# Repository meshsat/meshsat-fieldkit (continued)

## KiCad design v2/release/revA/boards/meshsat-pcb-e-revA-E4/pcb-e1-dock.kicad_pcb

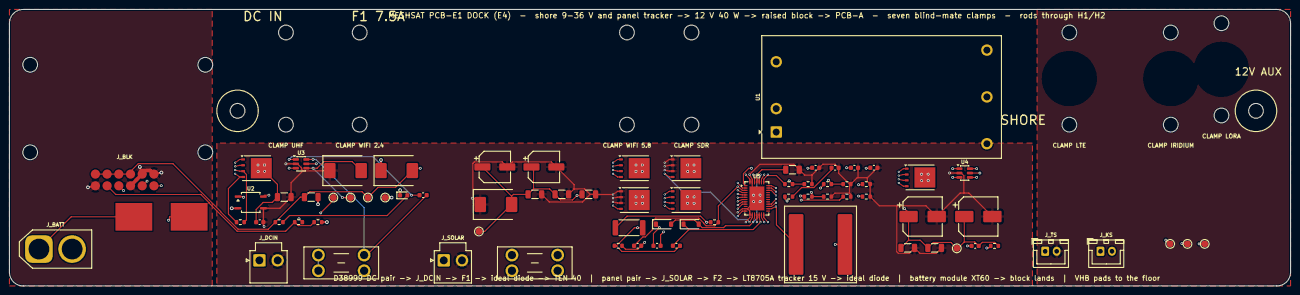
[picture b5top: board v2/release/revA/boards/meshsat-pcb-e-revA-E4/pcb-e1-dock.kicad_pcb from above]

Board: 4 copper layers, 278.0 x 60.0 mm, 97 parts (0 on the bottom side), 44 nets.

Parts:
C1, C13, C14: 10u 50V; C_1206_3216Metric
C2, C23: 100n; C_0603_1608Metric
C3: 22u 25V; C_1206_3216Metric
C4, C28: 100n 50V; C_0603_1608Metric
C11, C12: 100u 35V Panasonic EEHZK1V101XP hybrid polymer (7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; CP_Elec_6.3x7.7
C15: 4.7u 50V; C_1206_3216Metric
C16: 1n; C_0603_1608Metric
C17, C18: 470n 25V; C_0603_1608Metric
C19: 4.7u 25V; C_1206_3216Metric
C20: 1u; C_0603_1608Metric
C21: 4.7n; C_0603_1608Metric
C22: 100p; C_0603_1608Metric
C24, C25: 39u 35V Panasonic 35SVPF39M polymer (6.9 mm); CP_Elec_8x6.7
C26, C27: 10u 25V; C_1206_3216Metric
D1: SMCJ33A (input surge, datasheet 50 V 100 ms); D_SMC
D3: SMCJ15A; D_SMC
D4: SMCJ33A (panel surge); D_SMC
D5: BAT54 boost diode INTVCC -> BOOST1; D_SOD-123
D6: BAT54 boost diode INTVCC -> BOOST2; D_SOD-123
F1: 7.5 A mini blade (Keystone 3568 holder, in the cl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; Fuseholder_Blade_Mini_Keystone_3568
F2: 10 A mini blade (Keystone 3568 holder, in the cle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; Fuseholder_Blade_Mini_Keystone_3568
H1, H2: M3 rod pass-through, PCB-A standoff stands here; MountingHole_3.2mm_M3
H3, H4, H5, H6: M3 standoff, raised block; MountingHole_3.2mm_M3
H7, H8: M3, float clamp UHF; MountingHole_3.2mm_M3
H9, H10: M3, float clamp WIFI 2.4; MountingHole_3.2mm_M3
H11, H12: M3, float clamp WIFI 5.8; MountingHole_3.2mm_M3
H13, H14: M3, float clamp SDR; MountingHole_3.2mm_M3
H15, H16: M3, float clamp LTE; MountingHole_3.2mm_M3
H17, H18: M3, float clamp IRIDIUM; MountingHole_3.2mm_M3
H19, H20: M3, float clamp LORA; MountingHole_3.2mm_M3
J_BATT: battery module lead (XT60-M, 60 A): + - ; fused 4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; AMASS_XT60-M_1x02_P7.20mm_Vertical
J_BLK: solder lands for the 12 signal wires to the block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; PogoTargets_2x6
J_DCIN: shore DC in 9-36 V, lead from the D38999/20FC4PN 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; JST_VH_B2P-VH_1x02_P3.96mm_Vertical
J_KS: Kelvin sense lead from the module positive termin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; JST_XH_B2B-XH-A_1x02_P2.50mm_Vertical
J_SOLAR: bare 12 V class panel in, lead from the D38999 sp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; JST_VH_B2P-VH_1x02_P3.96mm_Vertical
J_TS: module thermistor lead (XH2.5): 103AT to the char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; JST_XH_B2B-XH-A_1x02_P2.50mm_Vertical
L1: 10uH Coilcraft XAL1510-103MED (Isat 26 A, 10.0 mm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; L_Coilcraft_XAL1510-103
LED1: green: shore 12 V present; LED_0603_1608Metric
P_CN: solder pad, 12 AWG wire to the block board return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; SolderPad_8x6
P_CP: solder pad, 12 AWG wire to the block board CELL+ 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; SolderPad_8x6
Q1, Q2: BSC039N06NS 60 V 3.9 mOhm N-FET (PG-TDSON-8: 1-3 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; TDSON-8-1
Q3: BSC028N06NS 60 V 2.8 mOhm N-FET, M1 buck top (TDS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; TDSON-8-1
Q4: BSC039N06NS 60 V N-FET, M2 buck bottom; TDSON-8-1
Q5: BSC028N06NS 60 V N-FET, M3 boost bottom; TDSON-8-1
Q6: BSC039N06NS 60 V N-FET, M4 boost top; TDSON-8-1
R1, R4, R18: 100k; R_0603_1608Metric
R2: 2.2k; R_0603_1608Metric
R3: 330R; R_0603_1608Metric
R5: 5 mOhm 1% 3 W 2512 RSENSE (RALEC LR2512-23R005F4); R_2512_6332Metric
R6, R7: 100R; R_0603_1608Metric
R8: 102k 1% (RFBIN1: panel point 17.6 V); R_0603_1608Metric
R9: 7.50k 1% (RFBIN2); R_0603_1608Metric
R10: 115k 1% (RFBOUT1: 15.1 V); R_0603_1608Metric
R11: 10.0k 1% (RFBOUT2); R_0603_1608Metric
R12: 215k 1% (RT: 202 kHz); R_0603_1608Metric
R13, R16, R17: 10k; R_0603_1608Metric
R14: 100k 1%; R_0603_1608Metric
R15: 15.0k 1% (SHDN: enable above about 9.5 V); R_0603_1608Metric
TP1: DC_IN; TestPoint_Pad_D1.5mm
TP2: DC_P; TestPoint_Pad_D1.5mm
TP3: SHORE_12V; TestPoint_Pad_D1.5mm
TP4: GND; TestPoint_Pad_D1.5mm
TP5: PV_P; TestPoint_Pad_D1.5mm
TP6: TRK_OUT; TestPoint_Pad_D1.5mm
TP7: BLK_SPARE; TestPoint_Pad_D1.5mm
TP8: CELL_P_MOD; TestPoint_Pad_D1.5mm
TP9: CELL_N_MOD; TestPoint_Pad_D1.5mm
U1: TRACO TEN 40-2412WIN: isolated 9-36 V in, 12 V 3.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; Converter_DCDC_TRACO_TEN40-110xxWIRH_THT
U2: EL817S / PC817 optocoupler: LED from PCB-A SHORE_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; SOP-4_3.8x4.1mm_P2.54mm
U3, U4: LM74700-Q1 ideal-diode controller: 1 VCAP 2 GND 3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; SOT-23-6
U5: LT8705A buck-boost controller, 38-lead QFN 5x7 (p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; WQFN-38-1EP_5x7mm_P0.5mm_EP3.15x5.15mm

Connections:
/BLK_SPARE: J_BLK.12, TP7.1
/CELL_N_MOD: J_BATT.2, P_CN.1, TP9.1
/CELL_P_MOD: J_BATT.1, P_CP.1, TP8.1
/CELL_SENSE_P: J_BLK.11, J_KS.1
/DC_F: C4.2, F1.2, Q1.1, Q1.2, Q1.3, R1.2, U3.3, U3.6
/DC_IN: F1.1, J_DCIN.1, TP1.1
/DC_N: C1.2, C2.2, C11.2, C12.2, C13.2, C14.2, C15.2, C19.2, C20.2, C21.2, C22.2, C23.2, C24.2, C25.2, C26.2, C27.2, D1.1, D4.1, J_DCIN.2, J_SOLAR.2, Q4.1, Q4.2, Q4.3, Q5.1, Q5.2, Q5.3, R9.2, R11.2, R12.2, R15.2, R16.2, R17.2, U1.2, U2.3, U3.2, U4.2, U5.11, U5.13, U5.37, U5.39
/DC_P: C1.1, C2.1, D1.2, Q1.5, Q2.5, TP2.1, U1.1, U3.4, U4.4
/LED_A: LED1.2, R2.2
/OPTO_A: R3.2, U2.1
/PV_IN: F2.1, J_SOLAR.1
/PV_P: C11.1, C12.1, C13.1, C14.1, C15.1, D4.2, F2.2, Q3.5, R8.1, R14.1, TP5.1, U5.32, U5.33, U5.34
/Q1_G: Q1.4, R1.1, U3.5
/Q2_G: Q2.4, R18.1, U4.5
/REMOTE: U1.3, U2.4
/SHORE_12V: C3.1, D3.2, J_BLK.1, J_BLK.2, J_BLK.3, J_BLK.4, R2.1, TP3.1, U1.4
/SHORE_INHIBIT: J_BLK.8, R3.1, R4.1
/TRK_BG1: Q4.4, U5.14
/TRK_BG2: Q5.4, U5.16
/TRK_BOOST1: C17.1, D5.1, U5.23
/TRK_BOOST2: C18.1, D6.1, U5.17
/TRK_CSN: C16.2, R7.2, U5.2
/TRK_CSP: C16.1, R6.2, U5.3
/TRK_FBIN: R8.2, R9.1, U5.5
/TRK_FBOUT: R10.2, R11.1, U5.6
/TRK_IMONI: R16.1, U5.38
/TRK_IMONO: R17.1, U5.7
/TRK_INTVCC: C19.1, D5.2, D6.2, U5.15, U5.35, U5.36
/TRK_LDO33: C20.1, U5.4
/TRK_LSENSE: L1.2, R5.1, R6.1
/TRK_OUT: C24.1, C25.1, C26.1, C27.1, C28.2, Q2.1, Q2.2, Q2.3, Q6.5, R10.1, R18.2, TP6.1, U4.3, U4.6, U5.29, U5.30, U5.31
/TRK_RT: R12.1, U5.12
/TRK_SHDN: R14.2, R15.1, U5.1
/TRK_SS: C23.1, U5.9
/TRK_SW1: C17.2, L1.1, Q3.1, Q3.2, Q3.3, Q4.5, U5.21
/TRK_SW2: C18.2, Q5.5, Q6.1, Q6.2, Q6.3, R5.2, R7.1, U5.19
/TRK_TG1: Q3.4, U5.22
/TRK_TG2: Q6.4, U5.18
/TRK_VC: C22.1, R13.1, U5.8
/TRK_VCC1: C21.1, R13.2
/TS_MOD: J_BLK.9, J_TS.1
/U3_VCAP: C4.1, U3.1
/U4_VCAP: C28.1, U4.1
GND: C3.2, D3.1, J_BLK.5, J_BLK.6, J_BLK.7, J_BLK.10, J_TS.2, LED1.1, R4.2, TP4.1, U1.5, U2.2

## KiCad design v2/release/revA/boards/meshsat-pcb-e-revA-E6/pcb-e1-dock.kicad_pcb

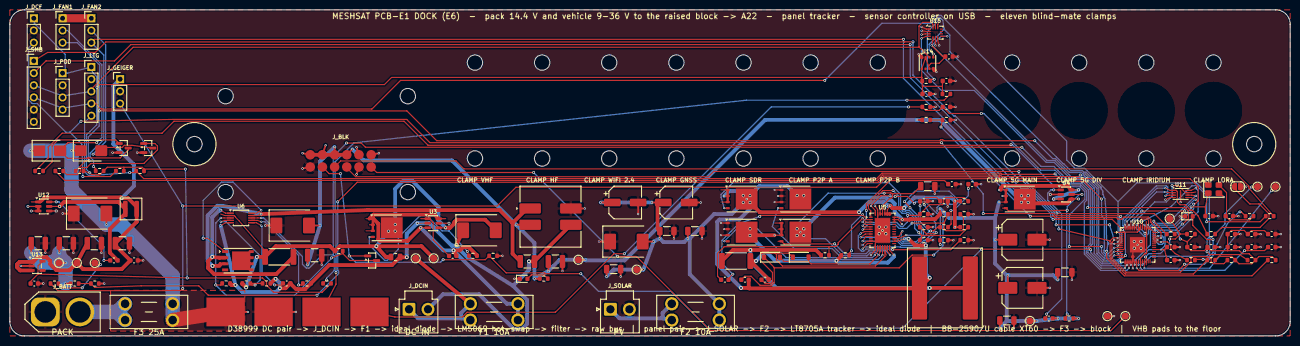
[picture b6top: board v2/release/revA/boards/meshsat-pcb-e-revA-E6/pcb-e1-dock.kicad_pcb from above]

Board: 4 copper layers, 267.0 x 68.0 mm, 189 parts (0 on the bottom side), 94 nets.

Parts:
C1, C31: 10u 25V 1210; C_1210_3225Metric
C2: 100n 100V; C_0805_2012Metric
C4, C28: 100n 50V; C_0603_1608Metric
C5: 100n (TIMER); C_0603_1608Metric
C6: 1u 100V 1210 (X, input side); C_1210_3225Metric
C7: 1u 100V 1210 (X, bus side); C_1210_3225Metric
C8: 10u 50V 1210; C_1210_3225Metric
C11, C12: 100u 35V Panasonic EEHZK1V101XP hybrid polymer (7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; CP_Elec_6.3x7.7
C13, C14: 10u 50V; C_1206_3216Metric
C15: 4.7u 50V; C_1206_3216Metric
C16: 1n; C_0603_1608Metric
C17, C18: 470n 25V; C_0603_1608Metric
C19: 4.7u 25V; C_1206_3216Metric
C20, C34, C35, C45, C46, C47: 1u; C_0603_1608Metric
C21: 4.7n; C_0603_1608Metric
C22: 100p; C_0603_1608Metric
C23, C30, C38, C39, C40, C41, C42, C43, C44, C48, C49, C50, C51: 100n; C_0603_1608Metric
C24, C25: 39u 35V Panasonic 35SVPF39M polymer (6.9 mm); CP_Elec_8x6.7
C26, C27: 10u 25V; C_1206_3216Metric
C32, C33: 22u 10V X7R 1210; C_1210_3225Metric
C36, C37: 15p; C_0603_1608Metric
D1: SMCJ33A (input surge, datasheet 50 V 100 ms); D_SMC
D2: SMCJ33A (bus clamp); D_SMC
D3: SMCJ18A (pack node clamp); D_SMC
D4: SMCJ33A (panel surge); D_SMC
D5: BAT54 boost diode INTVCC -> BOOST1; D_SOD-123
D6: BAT54 boost diode INTVCC -> BOOST2; D_SOD-123
D7: SS14 flyback across fan 1; D_SMB
D8: SS14 flyback across fan 2; D_SMB
F1: 10 A mini blade (Keystone 3568 holder): vehicle i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; Fuseholder_Blade_Mini_Keystone_3568
F2: 10 A mini blade (Keystone 3568 holder): panel inp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; Fuseholder_Blade_Mini_Keystone_3568
F3: 25 A mini blade (Keystone 3568 holder): pack to t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; Fuseholder_Blade_Mini_Keystone_3568
H1, H2: M3 rod pass-through, PCB-A standoff stands here; MountingHole_3.2mm_M3
H3, H4, H5, H6: M3 standoff, raised block; MountingHole_3.2mm_M3
H7, H8: M3, float clamp VHF; MountingHole_3.2mm_M3
H9, H10: M3, float clamp HF; MountingHole_3.2mm_M3
H11, H12: M3, float clamp WIFI 2.4; MountingHole_3.2mm_M3
H13, H14: M3, float clamp GNSS; MountingHole_3.2mm_M3
H15, H16: M3, float clamp SDR; MountingHole_3.2mm_M3
H17, H18: M3, float clamp P2P A; MountingHole_3.2mm_M3
H19, H20: M3, float clamp P2P B; MountingHole_3.2mm_M3
H21, H22: M3, float clamp 5G MAIN; MountingHole_3.2mm_M3
H23, H24: M3, float clamp 5G DIV; MountingHole_3.2mm_M3
H25, H26: M3, float clamp IRIDIUM; MountingHole_3.2mm_M3
H27, H28: M3, float clamp LORA; MountingHole_3.2mm_M3
JP1: BOOTSEL: short while powering to enter the USB bo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; SolderJumper-2_P1.3mm_Open_RoundedPad1.0x1.5mm
J_BATT: BB-2590/U cable (BTA-70762-2) on XT60-M: pin 2 (t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; AMASS_XT60-M_1x02_P7.20mm_Vertical
J_BLK: solder lands for the 12 signal wires to the block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; PogoTargets_2x6
J_DCF: DCF77 receiver module: 3.3 V, GND, pulse; PinHeader_1x03_P2.54mm_Vertical
J_DCIN: vehicle and shore DC in 9-36 V, lead from the D38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; JST_VH_B2P-VH_1x02_P3.96mm_Vertical
J_FAN1: mixer fan 1 under the plate (12 V class fan on th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; PinHeader_1x03_P2.54mm_Vertical
J_FAN2: mixer fan 2 under the plate (12 V class fan on th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; PinHeader_1x03_P2.54mm_Vertical
J_GEIGER: Geiger counter module (RadiationD-v1.1 class): 5 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; PinHeader_1x03_P2.54mm_Vertical
J_LTG: AS3935 lightning sensor module (CJMCU-3935 class)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; PinHeader_1x05_P2.54mm_Vertical
J_POD: outside sensor pod on the connector plate (M8 sea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; PinHeader_1x04_P2.54mm_Vertical
J_SMB: pack SMBus (XH or pin header): section A SDA SCL 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; PinHeader_1x06_P2.54mm_Vertical
J_SOLAR: bare 12 V class panel in, lead from the D38999 sp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; JST_VH_B2P-VH_1x02_P3.96mm_Vertical
L1: 10uH Coilcraft XAL1510-103MED (Isat 26 A, 10.0 mm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; L_Coilcraft_XAL1510-103
L2: Bourns SRF1260-4R7Y dual-winding choke (7.2 A per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; L_CommonModeChoke_Bourns_SRF1260
L3: 4.7uH XAL4020-472ME; L_Coilcraft_XAL4020-XXX
LED1: green: vehicle input present; LED_0603_1608Metric
LED2: status (GPIO25); LED_0603_1608Metric
PAD_W1: water electrode A (bare copper, +3.3 V through 1 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; SolderPad_8x6
PAD_W2: water electrode B (bare copper, to ADC0); SolderPad_8x6
P_CN: solder pad, 12 AWG wire to the block board return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; SolderPad_8x6
P_CP: solder pad, 12 AWG wire to the block board CELL+ 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; SolderPad_8x6
Q1, Q2: BSC039N06NS 60 V 3.9 mOhm N-FET (PG-TDSON-8: 1-3 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; TDSON-8-1
Q3: BSC028N06NS 60 V 2.8 mOhm N-FET, M1 buck top (TDS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; TDSON-8-1
Q4: BSC039N06NS 60 V N-FET, M2 buck bottom; TDSON-8-1
Q5: BSC028N06NS 60 V N-FET, M3 boost bottom; TDSON-8-1
Q6: BSC039N06NS 60 V N-FET, M4 boost top; TDSON-8-1
Q7: 60 V N-FET PowerPAK SO-8 (CSD19532Q5B class), hot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; PowerPAK_SO-8_Single
Q8: 2N7002: SHORE_INHIBIT high pulls UVLO low = input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; SOT-23
Q9: 2N7002 fan 1 low-side switch (1 G, 2 S, 3 D); SOT-23
Q10: 2N7002 fan 2 low-side switch (1 G, 2 S, 3 D); SOT-23
R1, R18, R26: 100k; R_0603_1608Metric
R5: 5 mOhm 1% 3 W 2512 RSENSE (RALEC LR2512-23R005F4); R_2512_6332Metric
R6, R7, R44, R45: 100R; R_0603_1608Metric
R8: 102k 1% (RFBIN1: panel point 17.6 V); R_0603_1608Metric
R9: 7.50k 1% (RFBIN2); R_0603_1608Metric
R10: 115k 1% (RFBOUT1: 15.1 V); R_0603_1608Metric
R11: 10.0k 1% (RFBOUT2); R_0603_1608Metric
R12: 215k 1% (RT: 202 kHz); R_0603_1608Metric
R13, R16, R17, R25, R31, R46, R47, R49, R50: 10k; R_0603_1608Metric
R14, R20, R22, R40, R42: 100k 1%; R_0603_1608Metric
R15: 15.0k 1% (SHDN: enable above about 9.5 V); R_0603_1608Metric
R19: 10mOhm 1% 2512 (hot-swap sense); R_2512_6332Metric
R21: 38.3k 1% (UVLO: 9 V); R_0603_1608Metric
R23: 6.65k 1% (OVLO: 40 V); R_0603_1608Metric
R24: 20k (PWR: power limit); R_0603_1608Metric
R27: 2.2k; R_0603_1608Metric
R28, R33: 1k; R_0603_1608Metric
R29, R30: 27R; R_0603_1608Metric
R32: 1k (BOOTSEL); R_0603_1608Metric
R34, R35, R36, R37: 4.7k; R_0603_1608Metric
R38, R39: 1M; R_0603_1608Metric
R41: 10k 1% (ADC1: 0.091 x bus); R_0603_1608Metric
R43: 22k 1% (ADC2: 0.18 x pack); R_0603_1608Metric
R48: 22R (pulse input series); R_0603_1608Metric
R51: 0R (CSB high: I2C mode; its own net keeps the pin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; R_0603_1608Metric
TP1: DC_IN; TestPoint_Pad_D1.5mm
TP2: DC_P; TestPoint_Pad_D1.5mm
TP3: VIN_RAW; TestPoint_Pad_D1.5mm
TP4: GND; TestPoint_Pad_D1.5mm
TP5: PV_P; TestPoint_Pad_D1.5mm
TP6: TRK_OUT; TestPoint_Pad_D1.5mm
TP7: BLK_SPARE; TestPoint_Pad_D1.5mm
TP8: CELL_F; TestPoint_Pad_D1.5mm
TP9: +5V_E6; TestPoint_Pad_D1.5mm
TP10: SWCLK; TestPoint_Pad_D1.5mm
TP11: SWDIO; TestPoint_Pad_D1.5mm
TP12: E6_RUN; TestPoint_Pad_D1.5mm
TP13: GEIGER_IN; TestPoint_Pad_D1.5mm
U3, U4: LM74700-Q1 ideal-diode controller: 1 VCAP 2 GND 3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; SOT-23-6
U5: LT8705A buck-boost controller, 38-lead QFN 5x7 (p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; WQFN-38-1EP_5x7mm_P0.5mm_EP3.15x5.15mm
U6: LM5069MM-2 hot-swap controller: 9 V on, 40 V off,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; VSSOP-10_3x3mm_P0.5mm
U10: RP2040 sensor controller (USB to B16 through the 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; QFN-56-1EP_7x7mm_P0.4mm_EP3.2x3.2mm
U11: W25Q16JVUXIQ 16 Mbit QSPI flash (USON-8: 1 CS 2 D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; Winbond_USON-8-1EP_3x2mm_P0.5mm_EP0.2x1.6mm
U12: AP63205WU-7 5 V 2 A buck for the controller, the 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; TSOT-23-6
U13: TLV75533PDBVR 3.3 V LDO; SOT-23-5
U14: BME688 inside climate: temperature, humidity, pre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; Bosch_LGA-8_3x3mm_P0.8mm_ClockwisePinNumbering
U15: BMI270 six-axis IMU (I2C 0x68): shock and tilt lo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; Bosch_LGA-14_3x2.5mm_P0.5mm
Y1: 12 MHz ABM8-272-T3 (3225): 1 XIN, 3 XOUT, 2 and 4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; Crystal_SMD_3225-4Pin_3.2x2.5mm

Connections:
/+3V3_E6: C35.1, C38.1, C39.1, C40.1, C41.1, C42.1, C43.1, C44.1, C47.1, C48.1, C49.1, C50.1, J_DCF.1, J_LTG.1, J_POD.1, R25.2, R31.2, R34.2, R35.2, R36.2, R37.2, R38.1, R46.2, R47.2, R49.2, R50.2, R51.1, U10.1, U10.10, U10.22, U10.33, U10.42, U10.43, U10.44, U10.48, U10.49, U11.8, U13.5, U14.2, U14.6, U14.8, U15.5, U15.8
/+5V_E6: C32.1, C33.1, C34.1, J_GEIGER.1, L3.2, TP9.1, U12.1, U13.1, U13.3
/BLK_SPARE: J_BLK.12, TP7.1
/BOOT_J: JP1.1, R32.2
/CELL+: F3.1, J_BATT.2
/CELL_F: C1.1, C31.1, D3.2, D7.1, D8.1, F3.2, J_FAN1.1, J_FAN2.1, P_CP.1, R42.1, TP8.1, U12.2, U12.3
/CELL_MON: R42.2, R43.1, U10.40
/DCF_PULSE: J_DCF.3, R49.1, U10.8
/DCIN_PGD: R25.1, U6.8, U10.15
/DC_F: C4.2, F1.2, Q1.1, Q1.2, Q1.3, R1.2, U3.3, U3.6
/DC_HS: C6.1, L2.1, Q7.3, U6.9
/DC_IN: F1.1, J_DCIN.1, TP1.1
/DC_P: C2.1, D1.2, Q1.5, R19.1, R20.1, R22.1, TP2.1, U3.4, U6.2
/E6_BST: C30.1, U12.6
/E6_DVDD: C45.1, C46.1, U10.23, U10.45, U10.50
/E6_RUN: R31.1, TP12.1, U10.26
/E6_SW: C30.2, L3.1, U12.5
/FAN1_G: Q9.1, R44.2
/FAN1_PWM: R44.1, U10.11
/FAN1_SW: D7.2, J_FAN1.2, Q9.3
/FAN1_TACH: J_FAN1.3, R46.1, U10.13
/FAN2_G: Q10.1, R45.2
/FAN2_PWM: R45.1, U10.12
/FAN2_SW: D8.2, J_FAN2.2, Q10.3
/FAN2_TACH: J_FAN2.3, R47.1, U10.14
/GEIGER_IN: R48.2, TP13.1
/GEIGER_PULSE: J_GEIGER.3, R48.1, U10.9
/GND_V: C2.2, C5.2, C6.2, D1.1, J_DCIN.2, L2.3, Q8.2, R21.2, R23.2, R24.2, U3.2, U6.5
/HS_GATE: Q7.1, U6.10
/HS_OVLO: R22.2, R23.1, U6.4
/HS_PWR: R24.1, U6.7
/HS_S: Q7.2, R19.2, U6.1
/HS_TIMER: C5.1, U6.6
/HS_UVLO: Q8.3, R20.2, R21.1, U6.3
/IMU_CSB: R51.2, U15.12
/IMU_INT1: U10.16, U15.4
/LED_A: LED1.2, R27.2
/LED_STAT: R33.1, U10.37
/LED_STAT_A: LED2.2, R33.2
/LTG_IRQ: J_LTG.5, R50.1, U10.17
/PV_IN: F2.1, J_SOLAR.1
/PV_P: C11.1, C12.1, C13.1, C14.1, C15.1, D4.2, F2.2, Q3.5, R8.1, R14.1, TP5.1, U5.32, U5.33, U5.34
/Q1_G: Q1.4, R1.1, U3.5
/Q2_G: Q2.4, R18.1, U4.5
/QSPI_D0: U10.53, U11.5
/QSPI_D1: U10.55, U11.2
/QSPI_D2: U10.54, U11.3
/QSPI_D3: U10.51, U11.7
/QSPI_SCLK: U10.52, U11.6
/QSPI_SS: R32.1, U10.56, U11.1
/SCL0: J_SMB.2, R35.1, U10.5
/SCL1: J_LTG.4, J_POD.4, J_SMB.4, R37.1, U10.7, U14.4, U15.13
/SDA0: J_SMB.1, R34.1, U10.4
/SDA1: J_LTG.3, J_POD.3, J_SMB.3, R36.1, U10.6, U14.3, U15.14
/SHORE_INHIBIT: J_BLK.8, Q8.1, R26.1, U10.18
/SWCLK: TP10.1, U10.24
/SWDIO: TP11.1, U10.25
/TRK_BG1: Q4.4, U5.14
/TRK_BG2: Q5.4, U5.16
/TRK_BOOST1: C17.1, D5.1, U5.23
/TRK_BOOST2: C18.1, D6.1, U5.17
/TRK_CSN: C16.2, R7.2, U5.2
/TRK_CSP: C16.1, R6.2, U5.3
/TRK_FBIN: R8.2, R9.1, U5.5
/TRK_FBOUT: R10.2, R11.1, U5.6
/TRK_IMONI: R16.1, U5.38
/TRK_IMONO: R17.1, U5.7
/TRK_INTVCC: C19.1, D5.2, D6.2, U5.15, U5.35, U5.36
/TRK_LDO33: C20.1, U5.4
/TRK_LSENSE: L1.2, R5.1, R6.1
/TRK_OUT: C24.1, C25.1, C26.1, C27.1, C28.2, Q2.1, Q2.2, Q2.3, Q6.5, R10.1, R18.2, TP6.1, U4.3, U4.6, U5.29, U5.30, U5.31
/TRK_RT: R12.1, U5.12
/TRK_SHDN: R14.2, R15.1, U5.1
/TRK_SS: C23.1, U5.9
/TRK_SW1: C17.2, L1.1, Q3.1, Q3.2, Q3.3, Q4.5, U5.21
/TRK_SW2: C18.2, Q5.5, Q6.1, Q6.2, Q6.3, R5.2, R7.1, U5.19
/TRK_TG1: Q3.4, U5.22
/TRK_TG2: Q6.4, U5.18
/TRK_VC: C22.1, R13.1, U5.8
/TRK_VCC1: C21.1, R13.2
/U3_VCAP: C4.1, U3.1
/U4_VCAP: C28.1, U4.1
/USB_DM_R: R30.1, U10.46
/USB_DP_R: R29.1, U10.47
/USB_E6_N: J_BLK.10, R30.2
/USB_E6_P: J_BLK.9, R29.2
/VIN_MON: R40.2, R41.1, U10.39
/VIN_RAW: C7.1, C8.1, D2.2, J_BLK.1, J_BLK.2, J_BLK.3, J_BLK.4, L2.2, Q2.5, R27.1, R40.1, TP3.1, U4.4
/WATER_A: PAD_W1.1, R38.2
/WATER_SENSE: C51.1, PAD_W2.1, R39.1, U10.38
/XIN: C36.1, U10.20, Y1.1
/XOUT: C37.1, R28.2, Y1.3
/XOUT_R: R28.1, U10.21
GND: C1.2, C7.2, C8.2, C11.2, C12.2, C13.2, C14.2, C15.2, C19.2, C20.2, C21.2, C22.2, C23.2, C24.2, C25.2, C26.2, C27.2, C31.2, C32.2, C33.2, C34.2, C35.2, C36.2, C37.2, C38.2, C39.2, C40.2, C41.2, C42.2, C43.2, C44.2, C45.2, C46.2, C47.2, C48.2, C49.2, C50.2, C51.2, D2.1, D3.1, D4.1, JP1.2, J_BATT.1, J_BLK.5, J_BLK.6, J_BLK.7, J_BLK.11, J_DCF.2, J_GEIGER.2, J_LTG.2, J_POD.2, J_SMB.5, J_SMB.6, J_SOLAR.2, L2.4, LED1.1, LED2.1, P_CN.1, Q4.1, Q4.2, Q4.3, Q5.1, Q5.2, Q5.3, Q9.2, Q10.2, R9.2, R11.2, R12.2, R15.2, R16.2, R17.2, R26.2, R39.2, R41.2, R43.2, TP4.1, U4.2, U5.11, U5.13, U5.37, U5.39, U10.19, U10.57, U11.4, U11.9, U12.4, U13.2, U14.1, U14.5, U14.7, U15.1, U15.2, U15.3, U15.6, U15.7, Y1.2, Y1.4
